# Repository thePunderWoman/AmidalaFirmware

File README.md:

<p align="center">

</p>

**Amidala** is an ESP32-S3 firmware for controlling your droids. It runs on the [Amidala PCB](PCB/) — a PCB designed to make wiring a full-featured droid build straightforward — and is compatible with both the N8R2 (8 MB flash) and N16R8 (16 MB flash) module variants.

> **[Amidala Wizards →](https://thepunderwoman.github.io/Amidala/)** — browser-based tools for setting up your droid. Includes a **Config Converter** for migrating Stealth RC / OG Amidala configs to the current format.

---

## Features

- **XBee wireless control** — secure, long-range, low-latency control via XBee 3 modules
- **Multiple Controller Support** — works with classic stealth controllers, Amidala controllers, standard Bluetooth gamepads, and analog RC (PPM) input.
- **Wi-Fi configuration UI** — browser-based interface for fully configuring your droid without needing to pull the SD card.
- **Native HCR support** — full Human Cyborg Relations vocalizer integration.
- **Advanced Dome Drive** — Built-in support for auto dome drive with a Pololu encoder motor and hall sensor, or any other basic PWM dome drive.
- **Flexible drive systems** — PWM, Sabertooth serial, or RoboteQ (PWM, serial, or hybrid)
- **Native built-in safety features** — Web based e-stop, dome obstruction motor disconnect, auto motor disable on controller disconnect.
- **Layers of controller button configurations** — with short-press, long-press, and alt-modifier layers
- **Effectively unlimited serial strings and gestures** — the only limits are your imagination!
- **And more** — I2C aux output, digital outputs, analog inputs, SD card config, servo outputs, and emergency stop handling

---

## Web Configuration UI

The Amidala web interface allows you total control over your droid's configuration. You can set up your controller configuration, which buttons trigger what, add serial commands, set defaults for audio, dome positioning, safety timeouts, emergency stop commands, configure Bluetooth, see digital pin statuses, use the serial monitor, configure your droid's gadgets, and even use the droid control page to trigger sequences, trigger emotes, and dome controls. See more in the wiki.

## Get Started

> **[Documentation Wiki →](https://github.com/thePunderWoman/Amidala/wiki)**

The wiki covers everything from first flash through full configuration. For a quick look at every available config key, see [example_config.txt](example_config.txt) — it's a complete annotated reference used on a real build. Although once you get set up initially, you won't need to look at this file again, as you can update every config option through the web UI.

---

## The Amidala PCB

The Amidala PCB is a purpose-built carrier for the ESP32-S3, designed to consolidate all the connectors a typical R2 build needs onto a single board:

- 4 servo headers (LEDC PWM)
- 4 digital output pins
- 2 analog inputs
- 3 serial headers (UART0 primary out, UART1 RoboClaw, UART2 aux)
- Auxiliary I2C header
- Native XBee slot (SPI, no adapter needed)
- Micro SD card reader
- Additional SPI breakout
- PPM input for RC receivers

> **[PCB details, schematics, and BOM →](PCB/)**

---

## License

This project is released under the [GNU General Public License v2](LICENSE). You are free to use, modify, and distribute it — including your own modifications — as long as you share the source code of any distributed derivatives under the same license.

---

## Contributing

Bug reports and feature requests are welcome — please use the [issue tracker](https://github.com/thePunderWoman/Amidala/issues).

If you'd like to contribute code, see [CONTRIBUTING.md](CONTRIBUTING.md).

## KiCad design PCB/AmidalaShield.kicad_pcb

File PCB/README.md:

# AmidalaBoard (AmidalaShield)

A custom KiCad PCB shield designed specifically for the [Amidala Firmware](https://github.com/thePunderWoman/AmidalaFirmware) — a control system for astromech and similar droid builds. This board provides all the I/O the firmware needs in a single, purpose-built package.

**Designed by [thePunderWoman](https://github.com/thePunderWoman)**

---

## Overview

The AmidalaShield is a carrier/breakout board for the **ESP32-S3 N16R8 DevKit**. It breaks out and conditions the ESP32-S3's peripherals for the specific needs of the Amidala Firmware: wireless XBee communication, multi-channel servo control, RC receiver input, SD card storage, and expansion headers for additional peripherals.

---

## Requirements

- **Microcontroller:** ESP32-S3 N16R8 DevKit (16 MB flash, 8 MB PSRAM)
- **Wireless modules:** XBee3 modules (x2 recommended — one for drive controller, one for dome controller)

---

## Hardware Features

### Wireless Communication
- **XBee3 module socket** for dual-controller operation (drive + dome)

### Servo Control
- **4× PWM servo outputs** — 3-pin headers (signal, power, ground)

### Serial Ports
- **2× hardware serial ports** — UART0 (shared with USB/programming) and UART1
- **1× software serial port** — for additional peripherals

### I/O
- **4× digital I/O pins**
- **2× analog input pins**
- **1× Aux I2C header** — for external I2C devices

### RC Control
- **PPM input (ppmin)** — for analog RC receiver

### Storage
- **Built-in microSD card reader** — used for `config.txt` at startup (matches Amidala Firmware config system)

### Expansion
- **Dedicated SPI header** — for external SPI peripherals

---

## Repository Contents

| File/Folder | Description |
|---|---|
| `AmidalaShield.kicad_sch` | Top-level schematic |
| `comms.kicad_sch` | XBee communications sub-sheet |
| `io.kicad_sch` | Digital/analog I/O sub-sheet |
| `power.kicad_sch` | Power distribution sub-sheet |
| `rc_control.kicad_sch` | RC input sub-sheet |
| `servos.kicad_sch` | Servo output sub-sheet |
| `spi.kicad_sch` | SPI header sub-sheet |
| `gerbers/` | Production-ready Gerber files |
| `libraries/` | Project-specific KiCad symbol/footprint libraries |
| `images/` | Board renders and screenshots |

---

## Getting Started

1. Clone this repo and open `AmidalaShield.kicad_pro` in KiCad 8+.
2. Review the schematics for pin assignments before assembling.
3. Use the Gerber files in `gerbers/` to order PCBs from your preferred fab.
4. Flash your ESP32-S3 with the [Amidala Firmware](https://github.com/thePunderWoman/AmidalaFirmware).
5. Place a `config.txt` on the microSD card — see the firmware repo for a full annotated example.

---

## GPIO Table

> **V1.1** — Updated GPIO assignments for ESP32-S3 WROOM-1 N8R2/N16R2 (Quad flash/PSRAM).
> Avoid GPIO35–37 on R8 (Octal) variants. GPIO48 reserved for onboard RGB LED.

| Function | GPIO | DevKit Side | Notes |
|---|---|---|---|
| **SPI MOSI** | GPIO11 | Left | Native FSPI, shared bus |
| **SPI MISO** | GPIO13 | Left | Native FSPI, shared bus |
| **SPI SCK** | GPIO12 | Left | Native FSPI, shared bus |
| **SD Card CS** | GPIO10 | Left | |
| **XBee CS** | GPIO7 | Left | |
| **SPI Spare CS** | GPIO14 | Left | Exposed header |
| **XBee ATTN** | GPIO16 | Left | |
| **XBee SLEEP** | GPIO15 | Left | |
| **I2C SDA** | GPIO8 | Left | Native I2C default |
| **I2C SCL** | GPIO9 | Left | Native I2C default |
| **UART0 TX** | GPIO43 | Right | Shared w/ USB — do not use simultaneously |
| **UART0 RX** | GPIO44 | Right | Shared w/ USB — do not use simultaneously |
| **UART1 TX** | GPIO17 | Right | Primary droid brain serial |
| **UART1 RX** | GPIO18 | Right | |
| **SW-UART TX** | GPIO21 | Right | |
| **SW-UART RX** | GPIO38 | Right | |
| **PPMIN** | GPIO47 | Right | |
| **Analog 1** | GPIO1 | Right | ADC1_0, WiFi-safe |
| **Analog 2** | GPIO2 | Right | ADC1_1, WiFi-safe |
| **Servo 1** | GPIO3 | Left | Strapping pin (JTAG source), safe after boot |
| **Servo 2** | GPIO4 | Left | |
| **Servo 3** | GPIO5 | Left | |
| **Servo 4** | GPIO6 | Left | |
| **Digital 1** | GPIO39 | Right | Goes HIGH after reset (not LOW like most GPIOs) |
| **Digital 2** | GPIO40 | Right | |
| **Digital 3** | GPIO41 | Right | |
| **Digital 4** | GPIO42 | Right | Transitions low on reset slightly slower |
| **RGB LED** | GPIO48 | Right | Reserved — onboard DevKit RGB LED |
| **NC** | GPIO8 | Left | Reserved |

### Pins Intentionally Avoided

| GPIO | Reason |
|---|---|
| GPIO0 | Strapping pin — boot mode |
| GPIO3 | Strapping pin — JTAG source (used for Servo 1, safe after boot) |
| GPIO19/20 | USB D-/D+ |
| GPIO26–32 | Internal SPI flash/PSRAM — never use |
| GPIO35–37 | Internal on Octal (R8) variants — safe on R2 only |
| GPIO45 | Strapping pin — VDD_SPI voltage |
| GPIO46 | Strapping pin |

---

## License

This hardware design is licensed under the [Creative Commons Attribution-NonCommercial-ShareAlike 4.0 International License](LICENSE.md) (CC BY-NC-SA 4.0).

You are free to share and adapt this design for non-commercial purposes, as long as you give appropriate credit and distribute any adaptations under the same license.

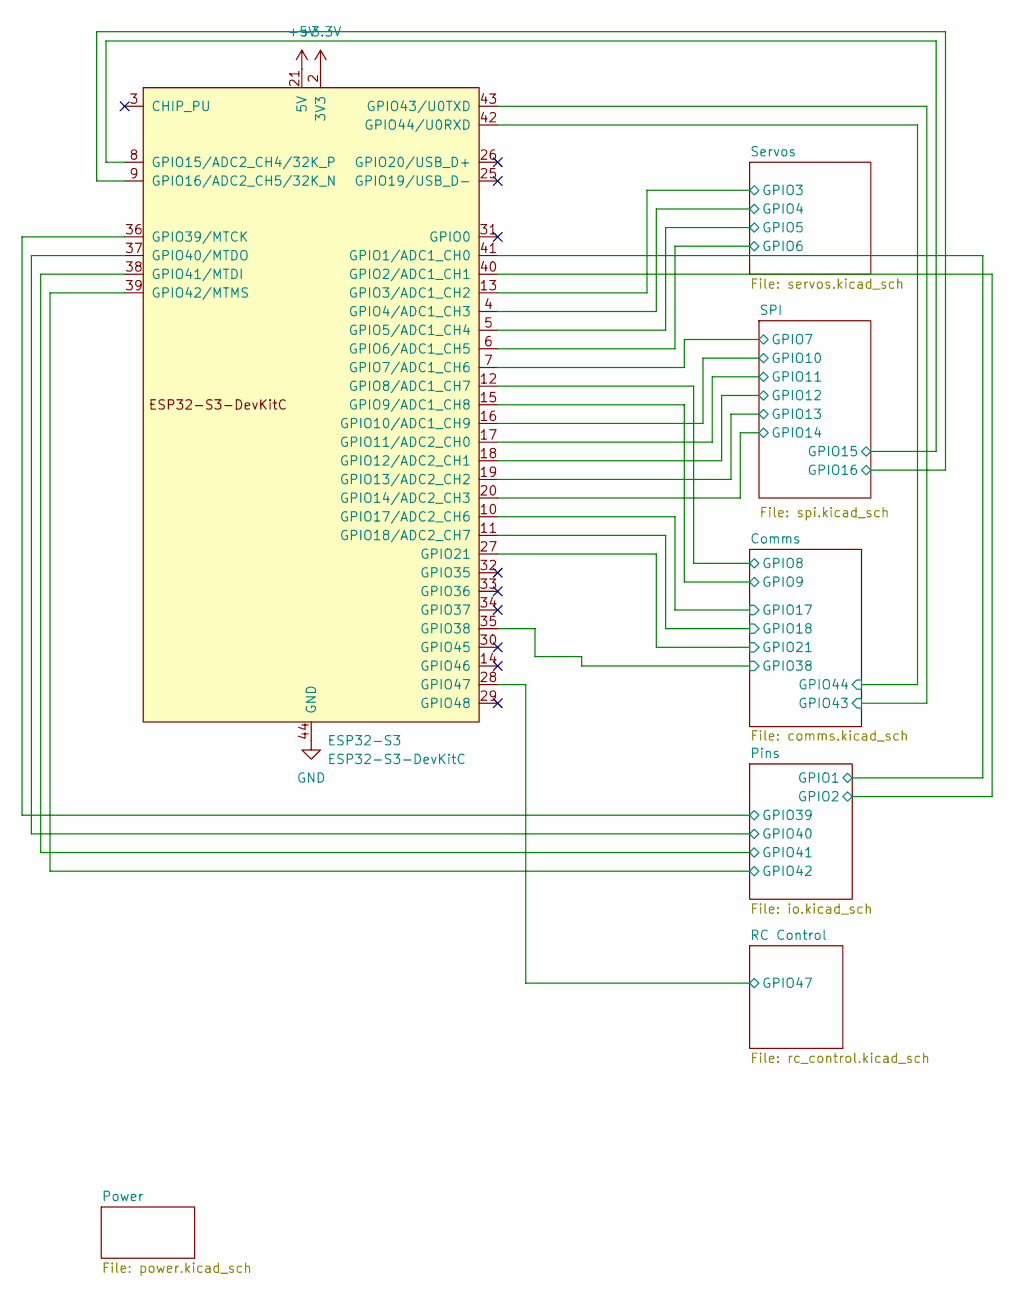
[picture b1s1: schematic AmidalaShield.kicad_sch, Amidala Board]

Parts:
ESP32-S3: ESP32-S3-DevKitC; ESP32-S2-DevKitC-1

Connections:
+3.3V: ESP32-S3.1 (3V3), ESP32-S3.2 (3V3); also elsewhere on the board
+5V: ESP32-S3.21 (5V); also elsewhere on the board
/Comms/GPIO8: ESP32-S3.12 (GPIO8/ADC1_CH7); also elsewhere on the board
/Comms/GPIO9: ESP32-S3.15 (GPIO9/ADC1_CH8); also elsewhere on the board
/Comms/GPIO17: ESP32-S3.10 (GPIO17/ADC2_CH6); also elsewhere on the board
/Comms/GPIO18: ESP32-S3.11 (GPIO18/ADC2_CH7); also elsewhere on the board
/Comms/GPIO21: ESP32-S3.27 (GPIO21); also elsewhere on the board
/Comms/GPIO38: ESP32-S3.35 (GPIO38); also elsewhere on the board
/Comms/GPIO43: ESP32-S3.43 (GPIO43/U0TXD); also elsewhere on the board
/Comms/GPIO44: ESP32-S3.42 (GPIO44/U0RXD); also elsewhere on the board
/Pins/GPIO1: ESP32-S3.41 (GPIO1/ADC1_CH0); also elsewhere on the board
/Pins/GPIO2: ESP32-S3.40 (GPIO2/ADC1_CH1); also elsewhere on the board
/Pins/GPIO39: ESP32-S3.36 (GPIO39/MTCK); also elsewhere on the board
/Pins/GPIO40: ESP32-S3.37 (GPIO40/MTDO); also elsewhere on the board
/Pins/GPIO41: ESP32-S3.38 (GPIO41/MTDI); also elsewhere on the board
/Pins/GPIO42: ESP32-S3.39 (GPIO42/MTMS); also elsewhere on the board
/RC Control/GPIO47: ESP32-S3.28 (GPIO47); also elsewhere on the board
/SPI/GPIO7: ESP32-S3.7 (GPIO7/ADC1_CH6); also elsewhere on the board
/SPI/GPIO10: ESP32-S3.16 (GPIO10/ADC1_CH9); also elsewhere on the board
/SPI/GPIO11: ESP32-S3.17 (GPIO11/ADC2_CH0); also elsewhere on the board
/SPI/GPIO12: ESP32-S3.18 (GPIO12/ADC2_CH1); also elsewhere on the board
/SPI/GPIO13: ESP32-S3.19 (GPIO13/ADC2_CH2); also elsewhere on the board
/SPI/GPIO14: ESP32-S3.20 (GPIO14/ADC2_CH3); also elsewhere on the board
/SPI/GPIO15: ESP32-S3.8 (GPIO15/ADC2_CH4/32K_P); also elsewhere on the board
/SPI/GPIO16: ESP32-S3.9 (GPIO16/ADC2_CH5/32K_N); also elsewhere on the board
/Servos/GPIO3: ESP32-S3.13 (GPIO3/ADC1_CH2); also elsewhere on the board
/Servos/GPIO4: ESP32-S3.4 (GPIO4/ADC1_CH3); also elsewhere on the board
/Servos/GPIO5: ESP32-S3.5 (GPIO5/ADC1_CH4); also elsewhere on the board
/Servos/GPIO6: ESP32-S3.6 (GPIO6/ADC1_CH5); also elsewhere on the board
GND: ESP32-S3.22 (GND), ESP32-S3.23 (GND), ESP32-S3.24 (GND), ESP32-S3.44 (GND); also elsewhere on the board

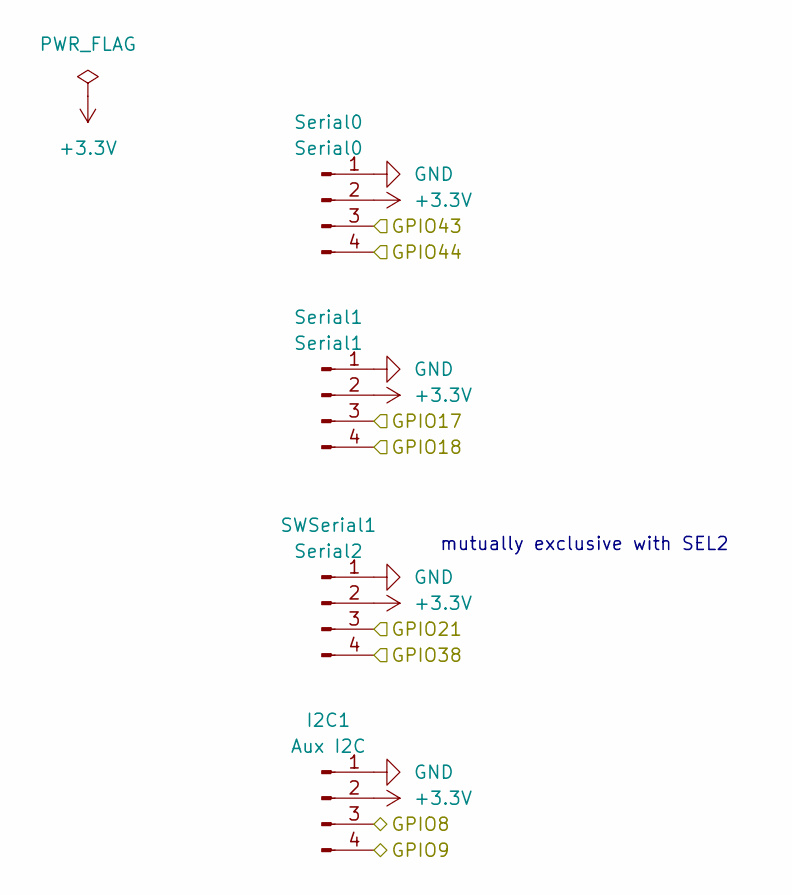
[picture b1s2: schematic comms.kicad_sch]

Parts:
I2C1: Aux I2C; PinHeader_1x04_P2.54mm_Vertical
SWSerial1: Serial2; PinHeader_1x04_P2.54mm_Vertical
Serial0: Serial0; PinHeader_1x04_P2.54mm_Vertical
Serial1: Serial1; PinHeader_1x04_P2.54mm_Vertical

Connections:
+3.3V: I2C1.2, SWSerial1.2, Serial0.2, Serial1.2; also elsewhere on the board
/Comms/GPIO8: I2C1.3; also elsewhere on the board
/Comms/GPIO9: I2C1.4; also elsewhere on the board
/Comms/GPIO17: Serial1.3; also elsewhere on the board
/Comms/GPIO18: Serial1.4; also elsewhere on the board
/Comms/GPIO21: SWSerial1.3; also elsewhere on the board
/Comms/GPIO38: SWSerial1.4; also elsewhere on the board
/Comms/GPIO43: Serial0.3; also elsewhere on the board
/Comms/GPIO44: Serial0.4; also elsewhere on the board
GND: I2C1.1, SWSerial1.1, Serial0.1, Serial1.1; also elsewhere on the board

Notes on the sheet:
mutually exclusive with SEL2

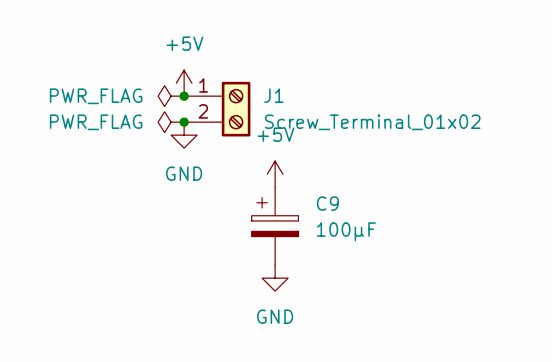
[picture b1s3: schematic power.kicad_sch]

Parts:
C9: 100µF; CP_EIA-3216-18_Kemet-A
J1: Screw_Terminal_01x02; TerminalBlock_Phoenix_MKDS-1,5-2-5.08_1x02_P5.08mm_Horizont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

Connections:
+5V: C9.1, J1.1; also elsewhere on the board
GND: C9.2, J1.2; also elsewhere on the board

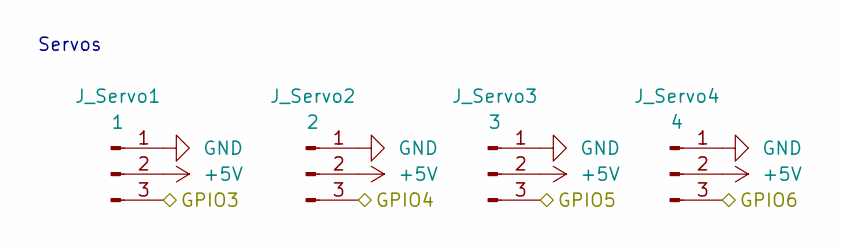
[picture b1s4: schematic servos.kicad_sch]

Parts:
J_Servo1: 1; PinHeader_1x03_P2.54mm_Vertical
J_Servo2: 2; PinHeader_1x03_P2.54mm_Vertical
J_Servo3: 3; PinHeader_1x03_P2.54mm_Vertical
J_Servo4: 4; PinHeader_1x03_P2.54mm_Vertical

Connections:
+5V: J_Servo1.2, J_Servo2.2, J_Servo3.2, J_Servo4.2; also elsewhere on the board
/Servos/GPIO3: J_Servo1.3; also elsewhere on the board
/Servos/GPIO4: J_Servo2.3; also elsewhere on the board
/Servos/GPIO5: J_Servo3.3; also elsewhere on the board
/Servos/GPIO6: J_Servo4.3; also elsewhere on the board
GND: J_Servo1.1, J_Servo2.1, J_Servo3.1, J_Servo4.1; also elsewhere on the board

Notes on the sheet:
Servos

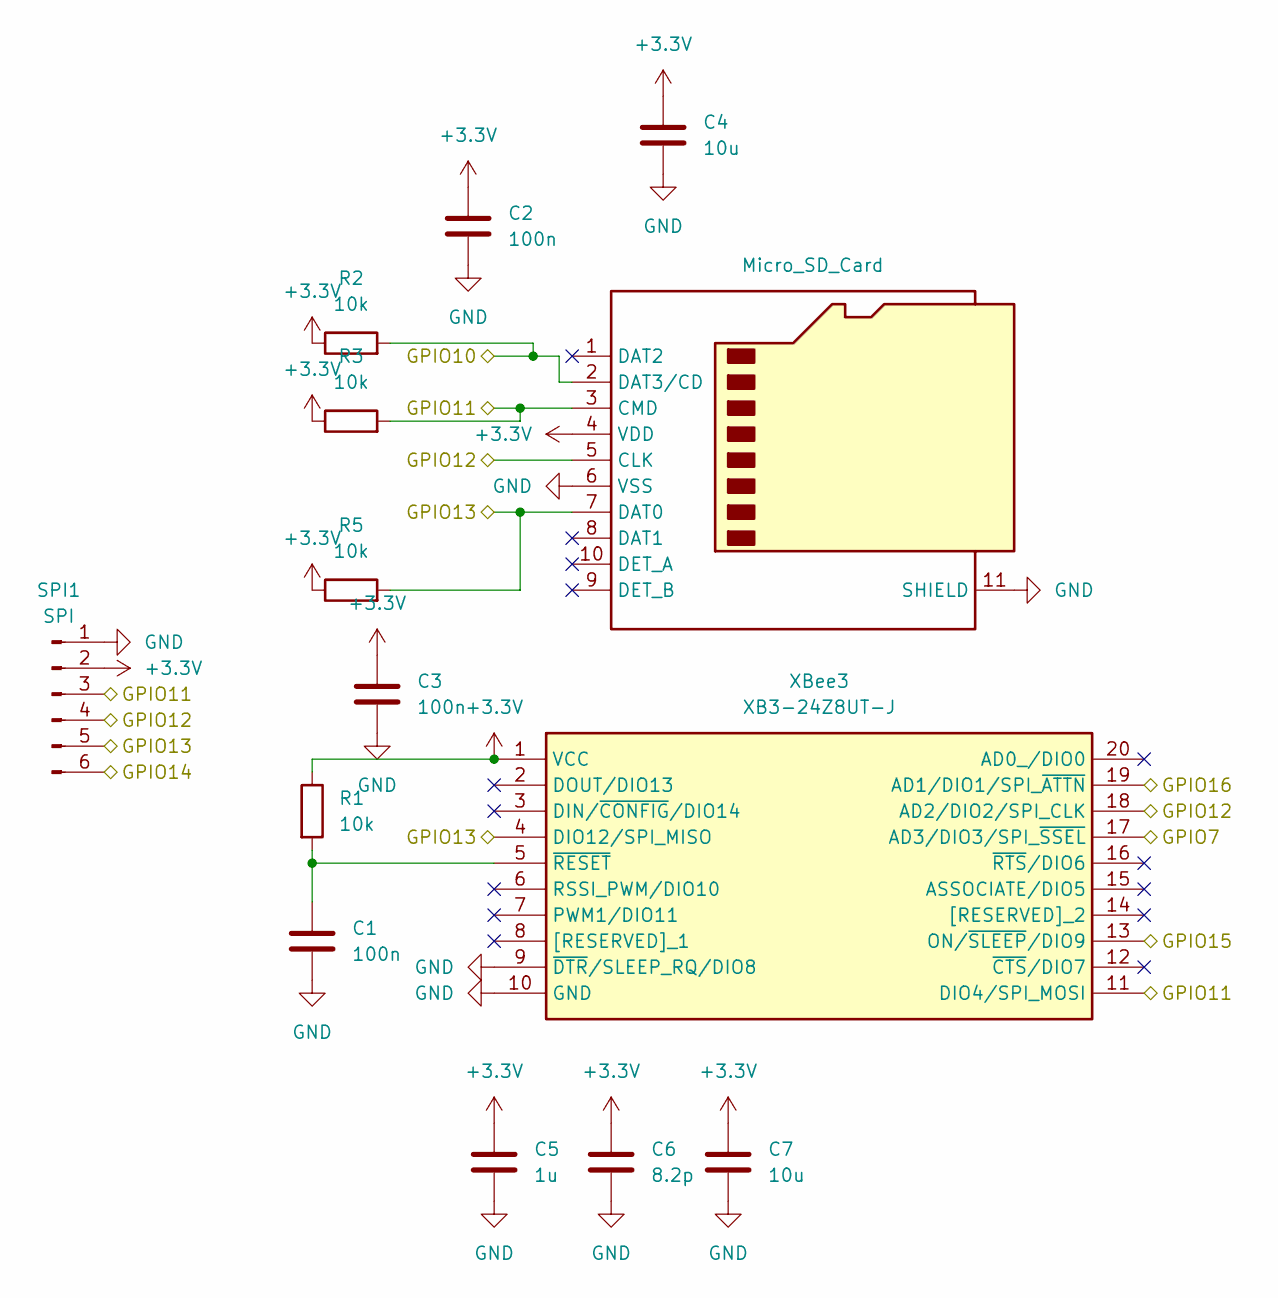
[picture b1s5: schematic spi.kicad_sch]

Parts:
C1, C2, C3: 100n; C_0603_1608Metric
C4, C7: 10u; C_0805_2012Metric
C5: 1u; C_0603_1608Metric
C6: 8.2p; C_0603_1608Metric
J3: Micro_SD_Card; microSD_HC_Hirose_DM3AT-SF-PEJM5
R1, R2, R3, R5: 10k; R_0603_1608Metric
SPI1: SPI; PinHeader_1x06_P2.54mm_Vertical
XBee3: XB3-24Z8UT-J; XB324Z8UTJ; Mouser Part Number 888-XB3-24Z8UT-J

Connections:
+3.3V: C2.1, C3.1, C4.1, C5.1, C6.1, C7.1, J3.4 (VDD), R1.1, R2.1, R3.1, R5.1, SPI1.2, XBee3.1 (VCC); also elsewhere on the board
/SPI/GPIO7: XBee3.17 (AD3/DIO3/SPI_~SSEL); also elsewhere on the board
/SPI/GPIO10: J3.2 (DAT3/CD), R2.2; also elsewhere on the board
/SPI/GPIO11: J3.3 (CMD), R3.2, SPI1.3, XBee3.11 (DIO4/SPI_MOSI); also elsewhere on the board
/SPI/GPIO12: J3.5 (CLK), SPI1.4, XBee3.18 (AD2/DIO2/SPI_CLK); also elsewhere on the board
/SPI/GPIO13: J3.7 (DAT0), R5.2, SPI1.5, XBee3.4 (DIO12/SPI_MISO); also elsewhere on the board
/SPI/GPIO14: SPI1.6; also elsewhere on the board
/SPI/GPIO15: XBee3.13 (ON/~SLEEP/DIO9); also elsewhere on the board
/SPI/GPIO16: XBee3.19 (AD1/DIO1/SPI_~ATTN); also elsewhere on the board
GND: C1.2, C2.2, C3.2, C4.2, C5.2, C6.2, C7.2, J3.6 (VSS), J3.11 (SHIELD), SPI1.1, XBee3.9 (~DTR/SLEEP_RQ/DIO8), XBee3.10 (GND); also elsewhere on the board
unnamed: C1.1, R1.2, XBee3.5 (~RESET)

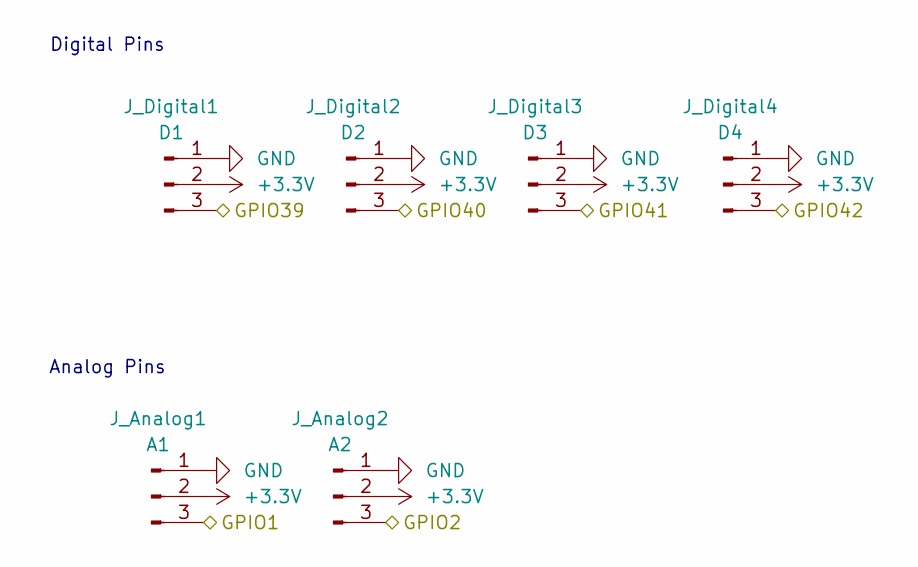
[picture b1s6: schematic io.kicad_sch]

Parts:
J_Analog1: A1; PinHeader_1x03_P2.54mm_Vertical
J_Analog2: A2; PinHeader_1x03_P2.54mm_Vertical
J_Digital1: D1; PinHeader_1x03_P2.54mm_Vertical
J_Digital2: D2; PinHeader_1x03_P2.54mm_Vertical
J_Digital3: D3; PinHeader_1x03_P2.54mm_Vertical
J_Digital4: D4; PinHeader_1x03_P2.54mm_Vertical

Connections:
+3.3V: J_Analog1.2, J_Analog2.2, J_Digital1.2, J_Digital2.2, J_Digital3.2, J_Digital4.2; also elsewhere on the board
/Pins/GPIO1: J_Analog1.3; also elsewhere on the board
/Pins/GPIO2: J_Analog2.3; also elsewhere on the board
/Pins/GPIO39: J_Digital1.3; also elsewhere on the board
/Pins/GPIO40: J_Digital2.3; also elsewhere on the board
/Pins/GPIO41: J_Digital3.3; also elsewhere on the board
/Pins/GPIO42: J_Digital4.3; also elsewhere on the board
GND: J_Analog1.1, J_Analog2.1, J_Digital1.1, J_Digital2.1, J_Digital3.1, J_Digital4.1; also elsewhere on the board

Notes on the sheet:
Analog Pins
Digital Pins

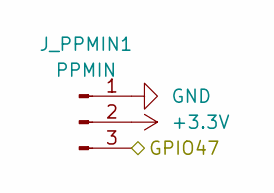
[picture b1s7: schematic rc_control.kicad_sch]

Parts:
J_PPMIN1: PPMIN; PinHeader_1x03_P2.54mm_Vertical

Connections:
+3.3V: J_PPMIN1.2; also elsewhere on the board
/RC Control/GPIO47: J_PPMIN1.3; also elsewhere on the board
GND: J_PPMIN1.1; also elsewhere on the board

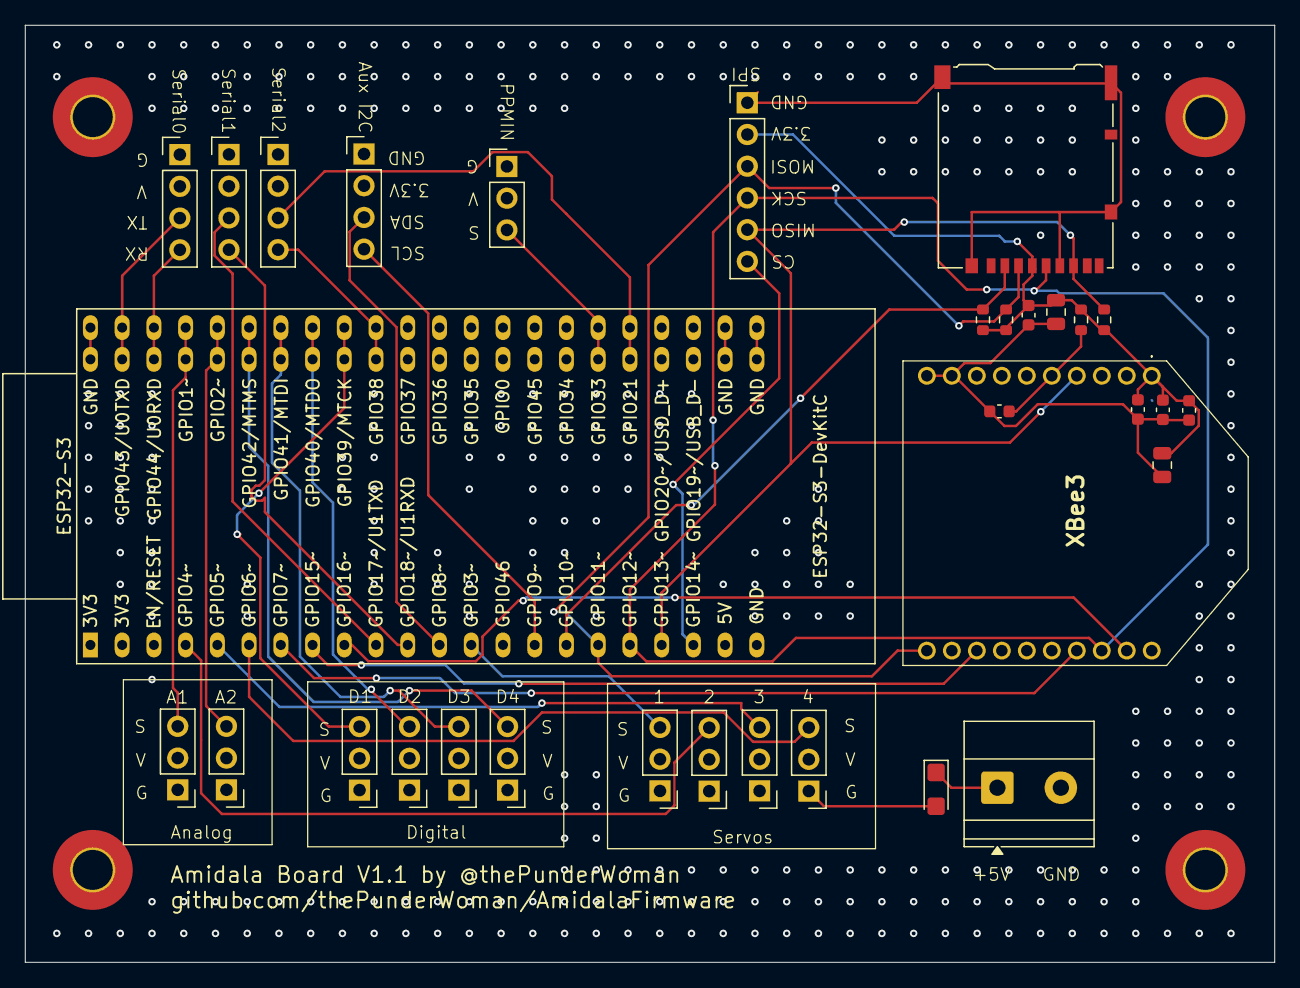
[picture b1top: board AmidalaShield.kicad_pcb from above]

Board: 4 copper layers, 100.0 x 75.0 mm, 32 parts (0 on the bottom side), 31 nets.

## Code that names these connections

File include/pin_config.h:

// pin_config.h
// Hardware pin assignments and serial port mappings for Amidala Firmware.
// All physical I/O pin numbers and serial port aliases are defined here so
// that wiring changes require edits in exactly one place.
//
// Target: ESP32-S3 WROOM1 N16R8 — Amidala custom PCB v1.1.
//
// Note: drive-system serial symbols (DOME_DRIVE_SERIAL, RDH_SERIAL) come from
// drive_config.h and must be resolved before this header is included.

#pragma once

// ---- Servo output pins (LEDC PWM via ServoDispatchESP32) --------------------
// 4 channels on this PCB (v1.1).

#define SERVO1_PIN  3
#define SERVO2_PIN  4
#define SERVO3_PIN  5
#define SERVO4_PIN  6

// ---- Digital output pins ----------------------------------------------------
// 4 channels on this PCB (v1.1).
// DRIVE_ACTIVE / DOME_ACTIVE are not wired; setDigitalPin() treats a 0 entry
// as absent.

#define DOUT1_PIN   39
#define DOUT2_PIN   40
#define DOUT3_PIN   41
#define DOUT4_PIN   42

// ---- Hall-effect sensor (RoboClaw dome drive) --------------------------------
// Wired to the Digital 2 header (GPIO40).  All ESP32-S3 GPIOs support
// external interrupts, so any digital pin would work here.

#define DOME_HALL_PIN  40

// ---- PPM RC input -----------------------------------------------------------

#define PPMIN_PIN   47

// ---- Analog inputs (ADC1, WiFi-safe) ----------------------------------------

#define ANALOG1_PIN  1   // ADC1_0
#define ANALOG2_PIN  2   // ADC1_1

// ---- SD card chip-select pin ------------------------------------------------

#define SD_CS_PIN   10

// ---- Mode select pin --------------------------------------------------------
// SEL2 A: available on GPIO21 unless AUX serial is enabled.
//   Define ESP32_AUX_SERIAL to use GPIO21/38 as UART2; SEL2 is then unavailable.

#ifndef ESP32_AUX_SERIAL
#define SEL2_PIN    21   // SEL2 A; SEL2 B (GPIO38) reserved for future 2-bit expansion
#endif

// ---- SPI bus pins -----------------------------------------------------------

#define SPI_MOSI_PIN      11
#define SPI_MISO_PIN      13
#define SPI_SCK_PIN       12
#define XBEE_CS_PIN        7
#define XBEE_ATTN_PIN     16
#define XBEE_SLEEP_PIN    15
#define SPI_SPARE_CS_PIN  14

// ---- I2C bus pins -----------------------------------------------------------

#define I2C_SDA_PIN  8
#define I2C_SCL_PIN  9

// ---- AUX serial (UART2 on SW-UART header) -----------------------------------
// Mutually exclusive with SEL2 A/B.  Enable with -DESP32_AUX_SERIAL.

#ifdef ESP32_AUX_SERIAL
#define AUX_SERIAL         Serial2
#define AUX_SERIAL_TX_PIN  21
#define AUX_SERIAL_RX_PIN  38
#endif

// ---- Serial port assignments ------------------------------------------------
// Serial  = USB-CDC console  (ARDUINO_USB_CDC_ON_BOOT=1)
// Serial0 = UART0 GPIO43/44  WCB / body controller out  (was Serial3 on Mega)
// Serial1 = UART1 GPIO17/18  RoboClaw dome drive         (see drive_config.h)

#define CONSOLE_SERIAL  Serial   // USB-CDC

// SERIAL (downstream WCB output) — ESP32 Arduino.h defines SERIAL as 0x0
// (a UART index constant).  Undefine it so we can use SERIAL as a Stream alias.
#if !defined(DOME_DRIVE_SERIAL) && !defined(RDH_SERIAL)
#undef  SERIAL
#define SERIAL  Serial0          // UART0, GPIO43/44 — WCB serial out
#endif

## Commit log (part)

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2026-03-01 Added SD Card read support
2026-03-01 Get everything working with some extras
2026-03-01 Added emergency stop on controller disconnect
2026-03-14 update config and add command string reference
2026-03-14 Integrates the human cyborg relations board as the default audio option
    This adds native support for the HCR board, fully swapping out all the native audio controls when the HCR board is selected.
2026-03-14 refactor: Added a full test suite
    Also moved all the code around to support the platformio environment.
2026-03-14 Updated platformio.ini file
2026-03-17 Add initialization delay for HCR audio settings
    This accounts for the board startup that necessarily happens when R2 starts up.
2026-03-17 refactor: ensure vmusic choice works
    This restores the ability to read the configuration from the vmusic2 if you so choose to run this on that hardware.
2026-03-22 Fix a few build issues
    this ensures the build is green and tests succeed.
2026-03-23 add github action for ci
    this adds a github action to keep builds green and tests running.
2026-04-05 Fix: make the muse toggle function properly
2026-04-12 fix: toggle behavior simplification
    This fixes some toggle behavior that was duplicating code, and or just did not toggle. It also adds some todos for the next session.
2026-04-19 Fix for speed script startup
2026-04-19 Use the correct mode and update max values
2026-04-19 Invert thumb wheel direction
2026-04-19 Update example config
2026-04-19 Updated example config again with more sequences
2026-04-25 removes dead code and updates example config
2026-05-04 fix: volume analog wheel bug
    Fixes a weird issue with the volume wheel where it drops low unexpectedly.
2026-05-07 Add delays between volume adjustment calls
    It seems HCR has issues if you send volume level commands too fast. So this adds a delay between calls.
2026-05-22 cleanup of reeltwo audio and any references to the mega
    Other than the readme, this should be a clean building and running esp32 build now with support targeting the amidala v1.0 board.
2026-06-19 fix: update Reeltwo library version to fix servo issues
    There was an upstream issue in the Reeltwo library
    that was preventing the servos from initializing
    and attaching correctly specifically for ESP32-S3.
    This fix bumps that version to 23.5.4, which
    includes the fix.
2026-06-22 Moved PCB repo into the main Amidala repo
    This moves all of the AmidalaBoard repo into this repo to consolidate the hardware and related firmware to one location.
2026-06-25 Add missing image files
    This adds the missing image assets for the readme.
2026-06-25 Add .code-workspace to .gitignore
2026-06-25 fix pin counts in readme
    This updates the pin info in the readme to make it more accurate to the board.
2026-06-27 Change artifact upload path to './wizard'
    This adds the github action for static pages deployment for the wizard pages.
2026-06-28 chore: set version to 1.0.1
